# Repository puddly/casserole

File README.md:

# Casserole
An open source alternative to the now-defunct [Green Bean adapter](https://github.com/GEMakers/green-bean) to monitor and control GE appliances through their RJ45 port.

# Installation

```sh
# Clone the repo
git clone https://github.com/puddly/casserole
cd casserole

# Setup a new virtual Python env (optional but recommended)
python3 -m venv venv
source venv/bin/activate

# Install dependencies
pip install -r requirements.txt

# Compile and upload the firmware to your ESP32
platformio run -t upload -v -e esp32 --upload-port=/dev/cu.SLAB_USBtoUART

# Run the host software and see what your appliance is doing
python protocol.py
```

## What works
1. All bus messages are sent back to the computer, including ones sent by the appliance user input boards.
2. Messages can be sent to the bus.

## What doesn't work
1. Other devices occasionally interrupt the adapter's messages. I'm not sure how devices take turns when sending data over the bus.
2. GE/FirstBuild's open source SDK is incomplete and does not document any way to remotely start some appliances (like my washer).

## Hardware
I don't know much about building electronics but here are the parts I've used:

 - ESP32 dev kit ([I use this one with built-in RGB LEDs](https://www.tindie.com/products/ddebeer/esp32-dev-board-wifibluetooth/) but any should work)
 - 3.3v to 5V bus transceiver ([TI SN74LVC2T45](https://www.ti.com/lit/ds/symlink/sn74lvc2t45.pdf))
 - 5V regulator ([ST LD1117](https://www.st.com/content/ccc/resource/technical/document/datasheet/99/3b/7d/91/91/51/4b/be/CD00000544.pdf/files/CD00000544.pdf/jcr:content/translations/en.CD00000544.pdf), though just about any should work). I've read that the ESP32 can draw up to 600mA in 100ms bursts when in AP mode but ordinarily draws about 40mA.

Wiring:

 - Regulate the 9V from the GE bus down to 5V and connect it both your ESP32's `Vin` pin and to the high voltage input of the bus transceiver.
 - Connect the ESP32's 3.3V pin to the low voltage input of the bus transceiver.
 - Tie together the ESP32's second UART's RX and TX pins (16 and 17) and connect them to the low voltage input of the bus transceiver.
 - Connect pin 18 (though any will work) to the direction control of the bus transceiver.

```
[insert proper diagram here]
```

## Low-level details

### RJ45 Port
The RJ45 (Ethernet) port on some GE appliances exposes a bus that allows for communication with the appliance's controller board. The three pins are labeled `GND`, `COMM`, and `9V`.

The COMM bus uses 5V logic and is an inverted UART at 19,200 baud.

### Protocol
I've been unable to acquire an actual Green Bean module so all of the information here is based on what I can capture from my washing machine. Here is a sample packet:

    e2 23 22 2d f1 03 f1 2e 0e 03 03 01 19 15 05 2a 00 0a f1 76 fc 0f 0a f1 39 01 03 f1 33 01 5d 9c 30 e3 e1

All packets begin with `e2` and end with `e3 e1` (although very rarely just `e3`). The byte `e0` acts as an escape character and all instances of `e0`, `e1`, `e2`, and `e3` in the body of the packet are escaped with `e0` (so `aa e0 bb e1 cc` becomes `aa e0 e0 bb e0 e1 cc`).

Each packet has a simple structure:
 
 - (1 byte) `e2`. Everything after this but before the final `e1` is encoded using the above scheme.
 - (1 byte) packet destination
 - (1 byte) total packet length (*before* the `e[0-3]` bytes have been escaped)
 - (1 byte) packet sender
 - (1 byte) command type
 - (? bytes) data
 - (2 bytes) CRC-16 checksum of the entire packet up until the start of the checksum bytes. It is a 16-bit CRC with the following parameters:

       width=16  poly=0x1021  init=0xe300  refin=false  refout=false  xorout=0x0000  check=0x5b10  residue=0x0000  name=(none)

    As before, this is computed on the packet payload before the `e[0-3]` bytes have been escaped. Interestingly, this specific CRC-16 has the following property:

       crc16(packet_until_checksum || crc16(packet_until_checksum)) == 0x0000

 - (1 or 2 bytes) `e1 e3`, although very rarely a packet is sent (consistently) with `e3` missing.

The packet command type determines how the `data` is interpreted. A command type of `f1` is used internally for all reads/writes and has the following structure:

 - (1 byte) `f1`
 - (1 byte) number of reads/writes encoded in `data`
 - A list of commands:
   - (1 byte) `f0` is read, `f1` is write.
   - (1 byte) endpoint ID
   - (1 byte) (This and the following bytes are absent in read requests and write acknowledgements) size of read respons or data to be written
   - (? bytes) data

The Green Bean uses a different syntax for reads (writes TBD) for what it calls ERDs:

 - (1 byte) `f0`
 - (1 byte) `01` for reads
 - (2 byte) 16-bit ERD, big-endian

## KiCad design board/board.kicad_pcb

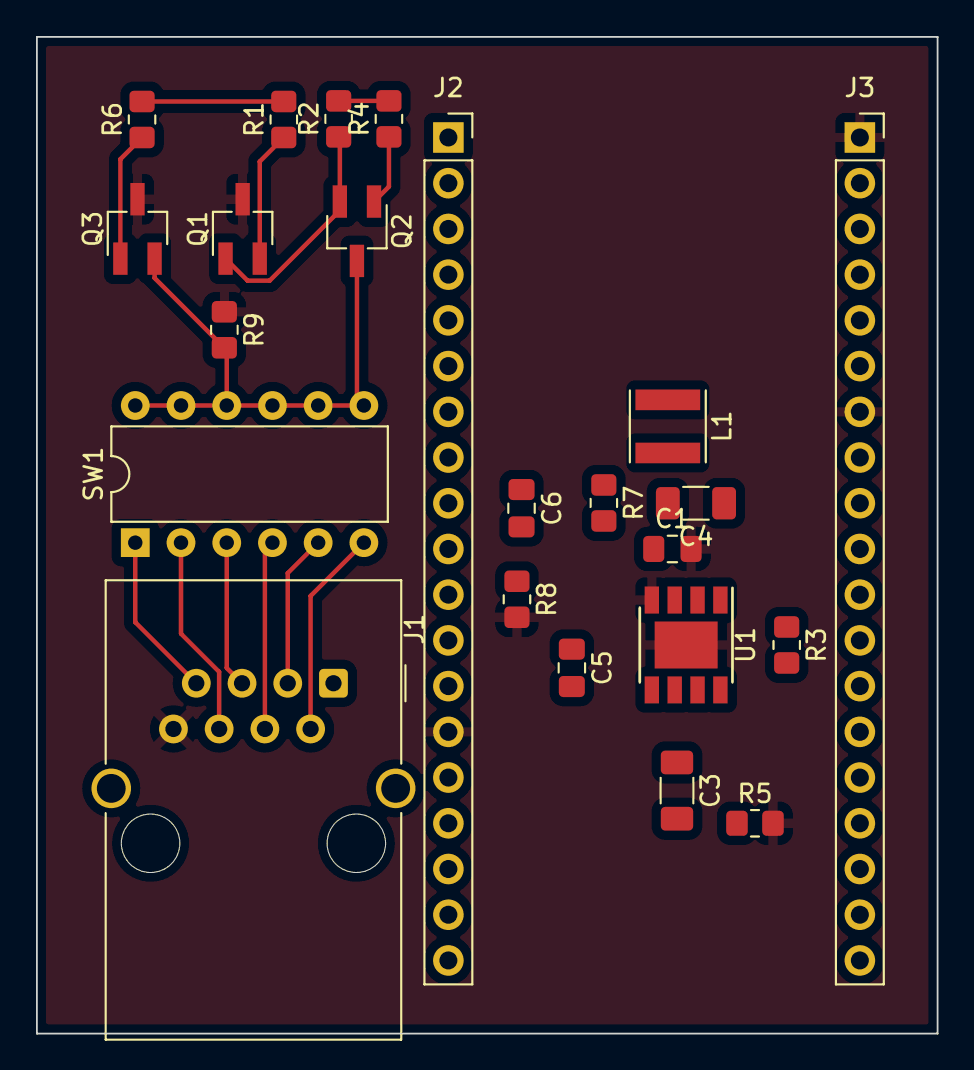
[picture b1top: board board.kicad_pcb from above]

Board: 2 copper layers, 50.0 x 55.4 mm, 23 parts (0 on the bottom side), 21 nets.

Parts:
C1: 10µF; C_0805_2012Metric_Pad1.18x1.45mm_HandSolder
C3: 6.8nF; C_1206_3216Metric_Pad1.33x1.80mm_HandSolder
C4: 10nF; C_1206_3216Metric_Pad1.33x1.80mm_HandSolder
C5, C6: 22µF; C_0805_2012Metric_Pad1.18x1.45mm_HandSolder
J1: RJ45; RJ45_Wuerth_7499010001A_Horizontal
J2, J3: Conn_01x19_Female; PinSocket_1x19_P2.54mm_Vertical
L1: 10µH; L_Vishay_IFSC-1515AH_4x4x1.8mm
Q1, Q2, Q3: Q_NMOS_DGS; SC-59_Handsoldering
R1, R9: ?; R_0805_2012Metric_Pad1.20x1.40mm_HandSolder
R2, R4, R6: 47k; R_0805_2012Metric_Pad1.20x1.40mm_HandSolder
R3: 100k; R_0805_2012Metric_Pad1.20x1.40mm_HandSolder
R5: 6.8k; R_0805_2012Metric_Pad1.20x1.40mm_HandSolder
R7: 53.3k; R_0805_2012Metric_Pad1.20x1.40mm_HandSolder
R8: 10k; R_0805_2012Metric_Pad1.20x1.40mm_HandSolder
SW1: SW_DIP_x06; DIP-12_W7.62mm
U1: AP6502; Diodes_SO-8EP

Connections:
+3V3: J2.1, R1.2, R6.2
+5V: C5.1, C6.1, J2.19, L1.2, R2.2, R4.2, R7.1
GEA_3.3V_RX: J3.12, Q3.1 (D), R6.1
GEA_3.3V_TX: J3.11, Q1.2 (G), R1.1
GEA_BUS: Q2.3 (S), Q3.2 (G), R9.2, SW1.7, SW1.8, SW1.9, SW1.10, SW1.11, SW1.12
GND: C1.2, J1.8, J2.14, J3.1, J3.7, Q1.3 (S), Q3.3 (S), R5.2, R8.2, R9.1, U1.4 (GND), U1.9 (EP)
unnamed: C3.1, U1.6 (COMP)
unnamed: C3.2, R5.1
unnamed: C4.1, U1.1 (BST)
unnamed: C4.2, L1.1, U1.3 (SW)
unnamed: C5.2, C6.2, R7.2, R8.1, U1.5 (FB)
unnamed: J1.2, SW1.6
unnamed: J1.3, SW1.5
unnamed: J1.4, SW1.4
unnamed: J1.5, SW1.3
unnamed: J1.6, SW1.2
unnamed: J1.7, SW1.1
unnamed: Q1.1 (D), Q2.2 (G), R2.1
unnamed: Q2.1 (D), R4.1
unnamed: R3.2, U1.7 (EN)
VCC: C1.1, J1.1, R3.1, U1.2 (IN)

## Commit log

2019-04-12 Initial commit.
2019-04-13 Replaced incorrect information about command IDs with info about lists of commands.
2019-04-13 Identified the checksum as a CRC-16 variant
2019-04-13 Added hacked together code
2019-04-15 Rewrote firmware to validate packets
2019-04-15 Removed unnecessary hacky debugging code from analyzer script
2019-04-15 Removed unnecessary hacky debugging code from dump script
2019-04-22 Completely decoded interface panel messages for my washer. Added untested write support to adapter.
2019-04-22 Added error packets to wrapper protocol and simplified packet parser in firmware.
2019-04-24 Initial attempt to get sending code in place
2019-04-24 Modified in-tree SoftwareSerial to be easier to use when RX_PIN == TX_PIN
2019-04-27 Transmission now works but crashes after ~10s.
2019-04-28 Implemented COBS for reliable framing. USB to adapter messages are occasionally corrupted but reliable transmission is now possible.
2019-04-29 Removed extraneous debugging code from firmware. Testing fuzzing of writable endpoints without success.
2019-04-29 Updated documentation
2019-05-09 Migrated to an ESP32 with chips for signal inversion and level shifting.
2019-05-10 Able to (briefly) control indicator lights on washer. No luck simulating the start button yet.
2019-05-25 Finally got "remote start" to work!
2020-01-18 Included slightly more detailed setup instructions. Removed washer-specific code from host software.
2021-11-30 Add WIP KiCad board files
2021-12-22 Organize into a Python module
2021-12-23 Rewrite GEA packet parser
2024-09-27 Create LICENSE
